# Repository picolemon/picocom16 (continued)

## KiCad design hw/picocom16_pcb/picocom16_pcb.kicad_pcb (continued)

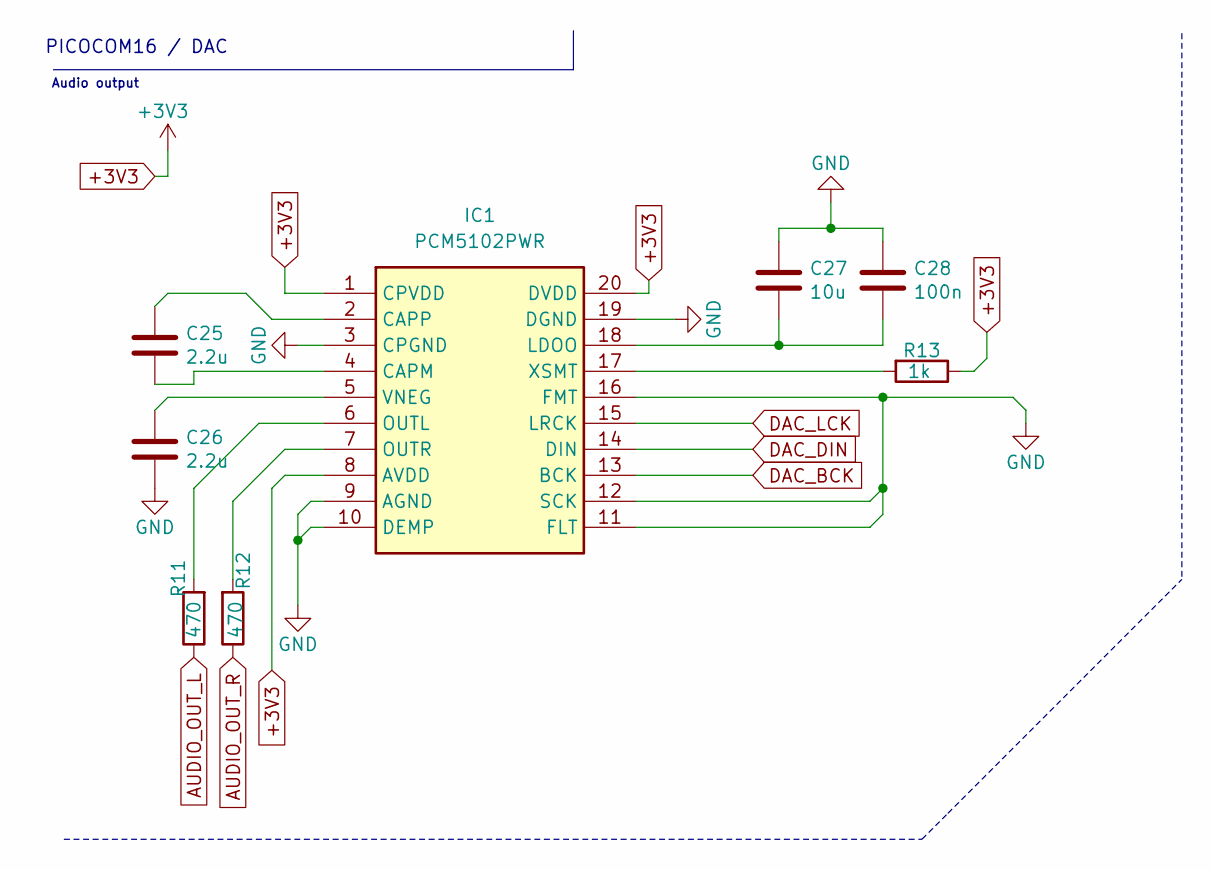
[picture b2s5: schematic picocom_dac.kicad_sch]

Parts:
C25, C26: 2.2u; C_0402_1005Metric
C27: 10u; C_0402_1005Metric
C28: 100n; C_0402_1005Metric
IC1: PCM5102PWR; SOP65P640X120-20N; Mouser Part Number 595-PCM5102PWR
R11, R12: 470; R_0402_1005Metric
R13: 1k; R_0402_1005Metric

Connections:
+3V3: IC1.1 (CPVDD), IC1.8 (AVDD), IC1.20 (DVDD), R13.1; also elsewhere on the board
AUDIO_OUT_L: R11.1; also elsewhere on the board
AUDIO_OUT_R: R12.1; also elsewhere on the board
DAC_BCK: IC1.13 (BCK); also elsewhere on the board
DAC_DIN: IC1.14 (DIN); also elsewhere on the board
DAC_LCK: IC1.15 (LRCK); also elsewhere on the board
GND: C26.2, C27.1, C28.1, IC1.3 (CPGND), IC1.9 (AGND), IC1.10 (DEMP), IC1.11 (FLT), IC1.12 (SCK), IC1.16 (FMT), IC1.19 (DGND); also elsewhere on the board
unnamed: C25.2, IC1.4 (CAPM)
unnamed: C25.1, IC1.2 (CAPP)
unnamed: C27.2, C28.2, IC1.18 (LDOO)
unnamed: IC1.6 (OUTL), R11.2
unnamed: IC1.7 (OUTR), R12.2
unnamed: C26.1, IC1.5 (VNEG)
unnamed: IC1.17 (XSMT), R13.2

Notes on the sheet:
PICOCOM16 / DAC
Audio output

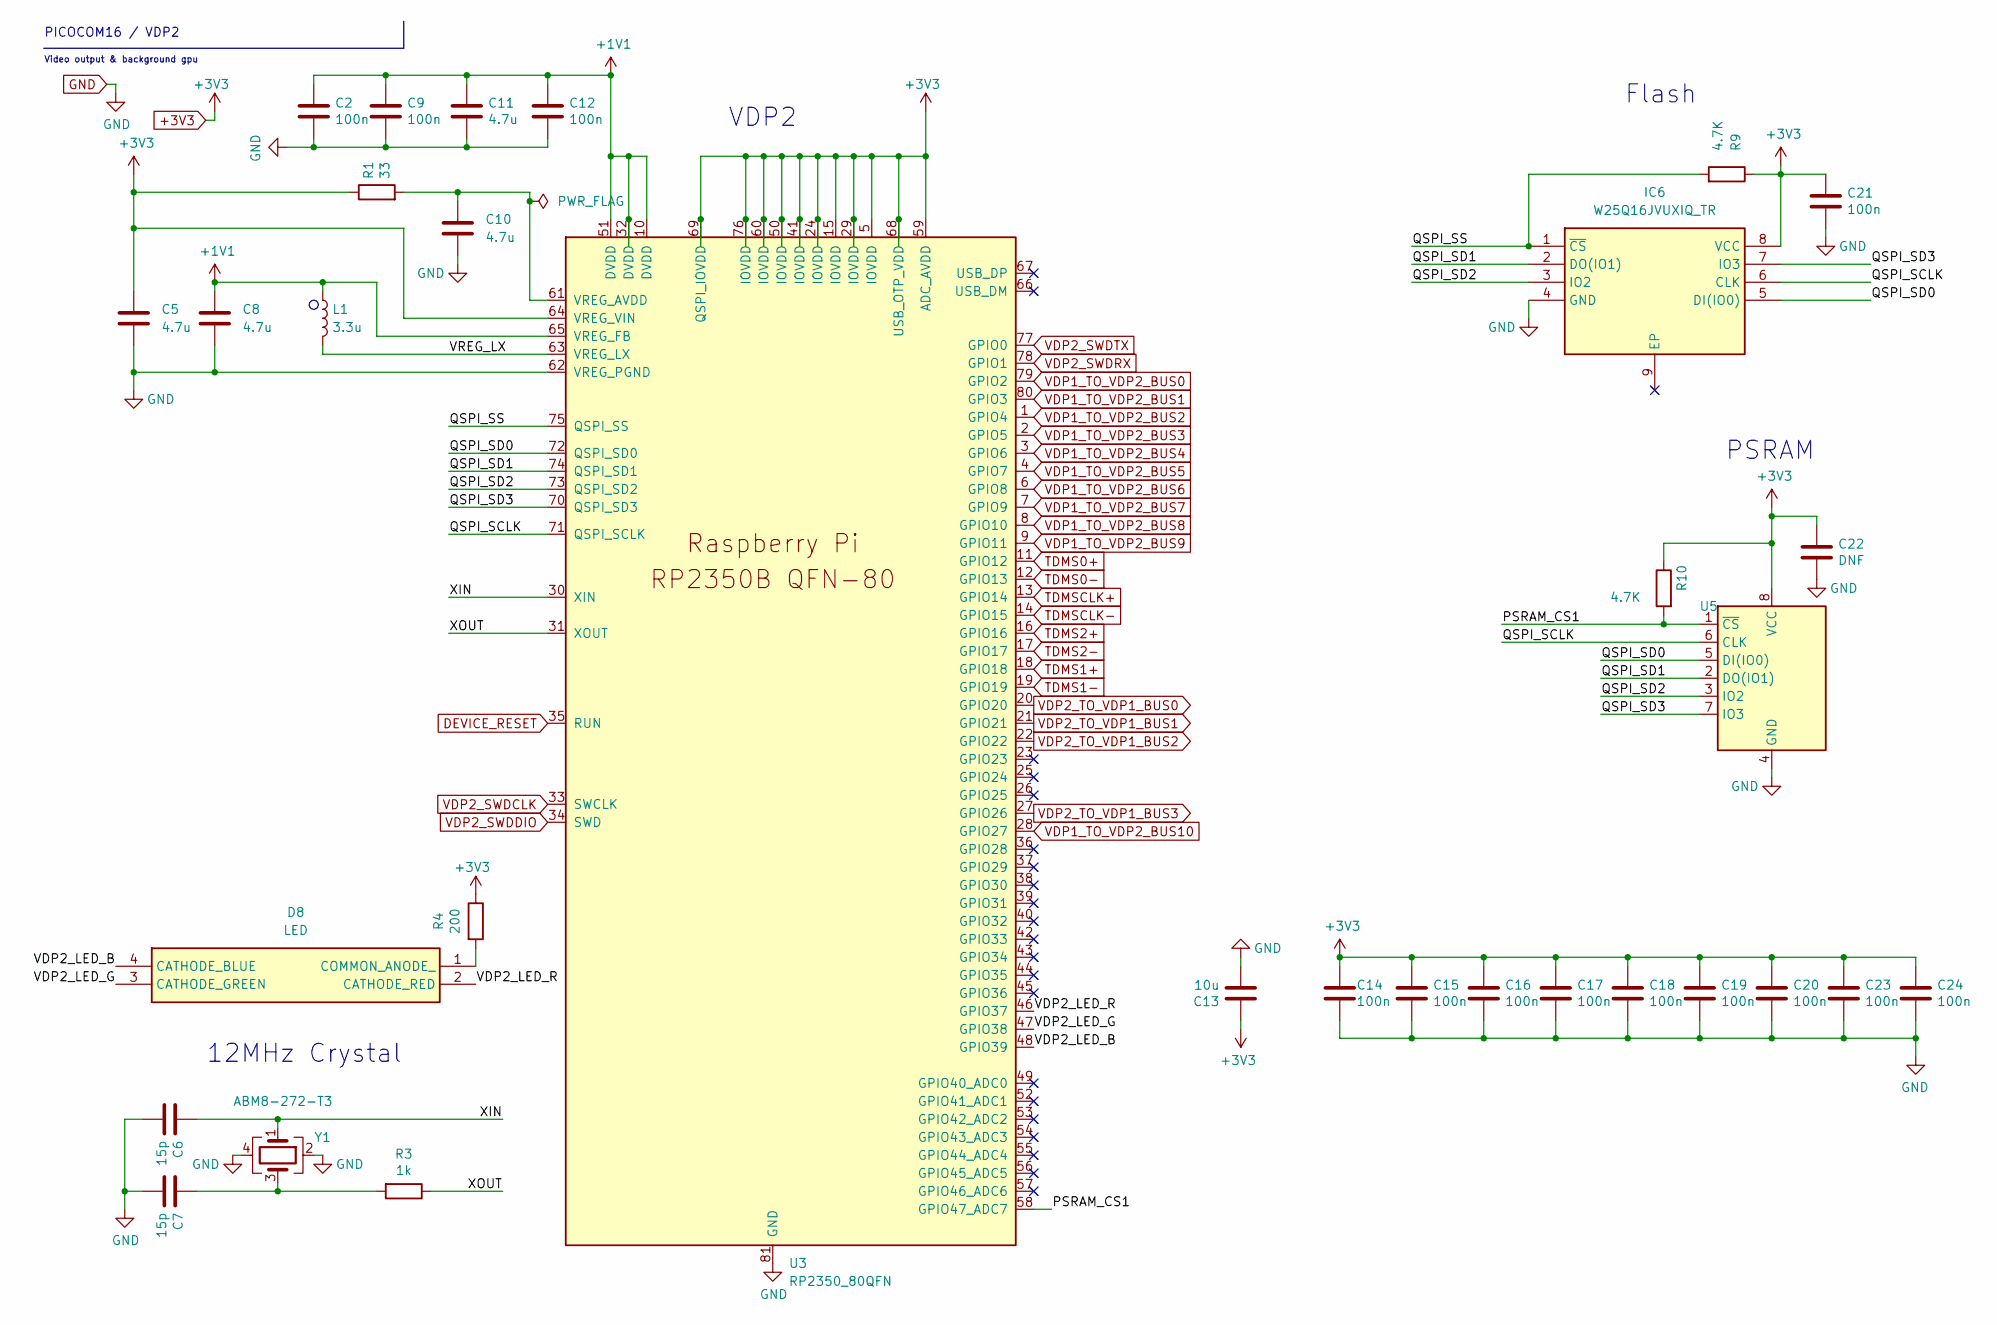
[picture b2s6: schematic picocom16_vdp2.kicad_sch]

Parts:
C2, C9, C12, C14, C15, C16, C17, C18, C19, C20, C21, C23, C24: 100n; C_0402_1005Metric
C5, C8, C10, C11: 4.7u; C_0402_1005Metric
C6, C7: 15p; C_0402_1005Metric
C13: 10u; C_0805_2012Metric
C22: DNF; C_0402_1005Metric
D8: LRTBR48G-P9Q7-1+R7S5-26+NP-68; LRTBR48GP9Q71R7S526NP68; Mouser Part Number 720-LRTBR48GP9A3521
IC6: W25Q16JVUXIQ_TR; SON50P300X200X60-9N; Mouser Part Number 454-W25Q16JVUXIQTR
L1: 3.3u; L_0805_2012Metric
R1: 33; R_0402_1005Metric
R3: 1k; R_0402_1005Metric
R4: 200; R_0402_1005Metric
R9, R10: 4.7K; R_0402_1005Metric
U3: RP2350_80QFN; RP2350-QFN-80-1EP_10x10_P0.4mm_EP3.4x3.4mm_ThermalVias
U5: SOIC-8_5.23x5.23mm_P1.27mm
Y1: ABM8-272-T3; ABM8272T3

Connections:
+1V1: C2.1, C8.1, C9.1, C11.1, C12.1, L1.1, U3.10 (DVDD), U3.32 (DVDD), U3.51 (DVDD), U3.65 (VREG_FB); also elsewhere on the board
+3V3: C5.1, C13.1, C14.1, C15.1, C16.1, C17.1, C18.1, C19.1, C20.1, C21.1, C22.1, C23.1, C24.1, IC6.8 (VCC), R1.1, R4.1, R9.1, R10.1, U3.5 (IOVDD), U3.15 (IOVDD), U3.24 (IOVDD), U3.29 (IOVDD), U3.41 (IOVDD), U3.50 (IOVDD), U3.59 (ADC_AVDD), U3.60 (IOVDD), U3.64 (VREG_VIN), U3.68 (USB_OTP_VDD), U3.69 (QSPI_IOVDD), U3.76 (IOVDD), U5.8 (VCC); also elsewhere on the board
/VDP2/PSRAM_CS1: R10.2, U3.58 (GPIO47_ADC7), U5.1 (~CS)
/VDP2/QSPI_SCLK: IC6.6 (CLK), U3.71 (QSPI_SCLK), U5.6 (CLK)
/VDP2/QSPI_SD0: IC6.5 (DI(IO0)), U3.72 (QSPI_SD0), U5.5 (DI(IO0))
/VDP2/QSPI_SD1: IC6.2 (DO(IO1)), U3.74 (QSPI_SD1), U5.2 (DO(IO1))
/VDP2/QSPI_SD2: IC6.3 (IO2), U3.73 (QSPI_SD2), U5.3 (IO2)
/VDP2/QSPI_SD3: IC6.7 (IO3), U3.70 (QSPI_SD3), U5.7 (IO3)
/VDP2/QSPI_SS: IC6.1 (~CS), R9.2, U3.75 (QSPI_SS)
/VDP2/VDP2_LED_B: D8.4 (CATHODE_BLUE), U3.48 (GPIO39)
/VDP2/VDP2_LED_G: D8.3 (CATHODE_GREEN), U3.47 (GPIO38)
/VDP2/VDP2_LED_R: D8.2 (CATHODE_RED), U3.46 (GPIO37)
/VDP2/VREG_LX: L1.2, U3.63 (VREG_LX)
/VDP2/XIN: C6.1, U3.30 (XIN), Y1.1
/VDP2/XOUT: R3.1, U3.31 (XOUT)
DEVICE_RESET: U3.35 (RUN); also elsewhere on the board
GND: C2.2, C5.2, C6.2, C7.2, C8.2, C9.2, C10.2, C11.2, C12.2, C13.2, C14.2, C15.2, C16.2, C17.2, C18.2, C19.2, C20.2, C21.2, C22.2, C23.2, C24.2, IC6.4 (GND), U3.62 (VREG_PGND), U3.81 (GND), U5.4 (GND), Y1.2, Y1.4; also elsewhere on the board
unnamed: C7.1, R3.2, Y1.3
unnamed: D8.1 (COMMON_ANODE_), R4.2
unnamed: C10.1, R1.2, U3.61 (VREG_AVDD)
TDMS0+: U3.11 (GPIO12); also elsewhere on the board
TDMS0-: U3.12 (GPIO13); also elsewhere on the board
TDMS1+: U3.18 (GPIO18); also elsewhere on the board
TDMS1-: U3.19 (GPIO19); also elsewhere on the board
TDMS2+: U3.16 (GPIO16); also elsewhere on the board
TDMS2-: U3.17 (GPIO17); also elsewhere on the board
TDMSCLK+: U3.13 (GPIO14); also elsewhere on the board
TDMSCLK-: U3.14 (GPIO15); also elsewhere on the board
VDP1_TO_VDP2_BUS0: U3.79 (GPIO2); also elsewhere on the board
VDP1_TO_VDP2_BUS1: U3.80 (GPIO3); also elsewhere on the board
VDP1_TO_VDP2_BUS2: U3.1 (GPIO4); also elsewhere on the board
VDP1_TO_VDP2_BUS3: U3.2 (GPIO5); also elsewhere on the board
VDP1_TO_VDP2_BUS4: U3.3 (GPIO6); also elsewhere on the board
VDP1_TO_VDP2_BUS5: U3.4 (GPIO7); also elsewhere on the board
VDP1_TO_VDP2_BUS6: U3.6 (GPIO8); also elsewhere on the board
VDP1_TO_VDP2_BUS7: U3.7 (GPIO9); also elsewhere on the board
VDP1_TO_VDP2_BUS8: U3.8 (GPIO10); also elsewhere on the board
VDP1_TO_VDP2_BUS9: U3.9 (GPIO11); also elsewhere on the board
VDP1_TO_VDP2_BUS10: U3.28 (GPIO27); also elsewhere on the board
VDP2_SWDCLK: U3.33 (SWCLK); also elsewhere on the board
VDP2_SWDDIO: U3.34 (SWD); also elsewhere on the board
VDP2_SWDRX: U3.78 (GPIO1); also elsewhere on the board
VDP2_SWDTX: U3.77 (GPIO0); also elsewhere on the board
VDP2_TO_VDP1_BUS0: U3.20 (GPIO20); also elsewhere on the board
VDP2_TO_VDP1_BUS1: U3.21 (GPIO21); also elsewhere on the board
VDP2_TO_VDP1_BUS2: U3.22 (GPIO22); also elsewhere on the board
VDP2_TO_VDP1_BUS3: U3.27 (GPIO26); also elsewhere on the board

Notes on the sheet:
PSRAM
Flash
VDP2
12MHz Crystal
PICOCOM16 / VDP2
Video output & background gpu

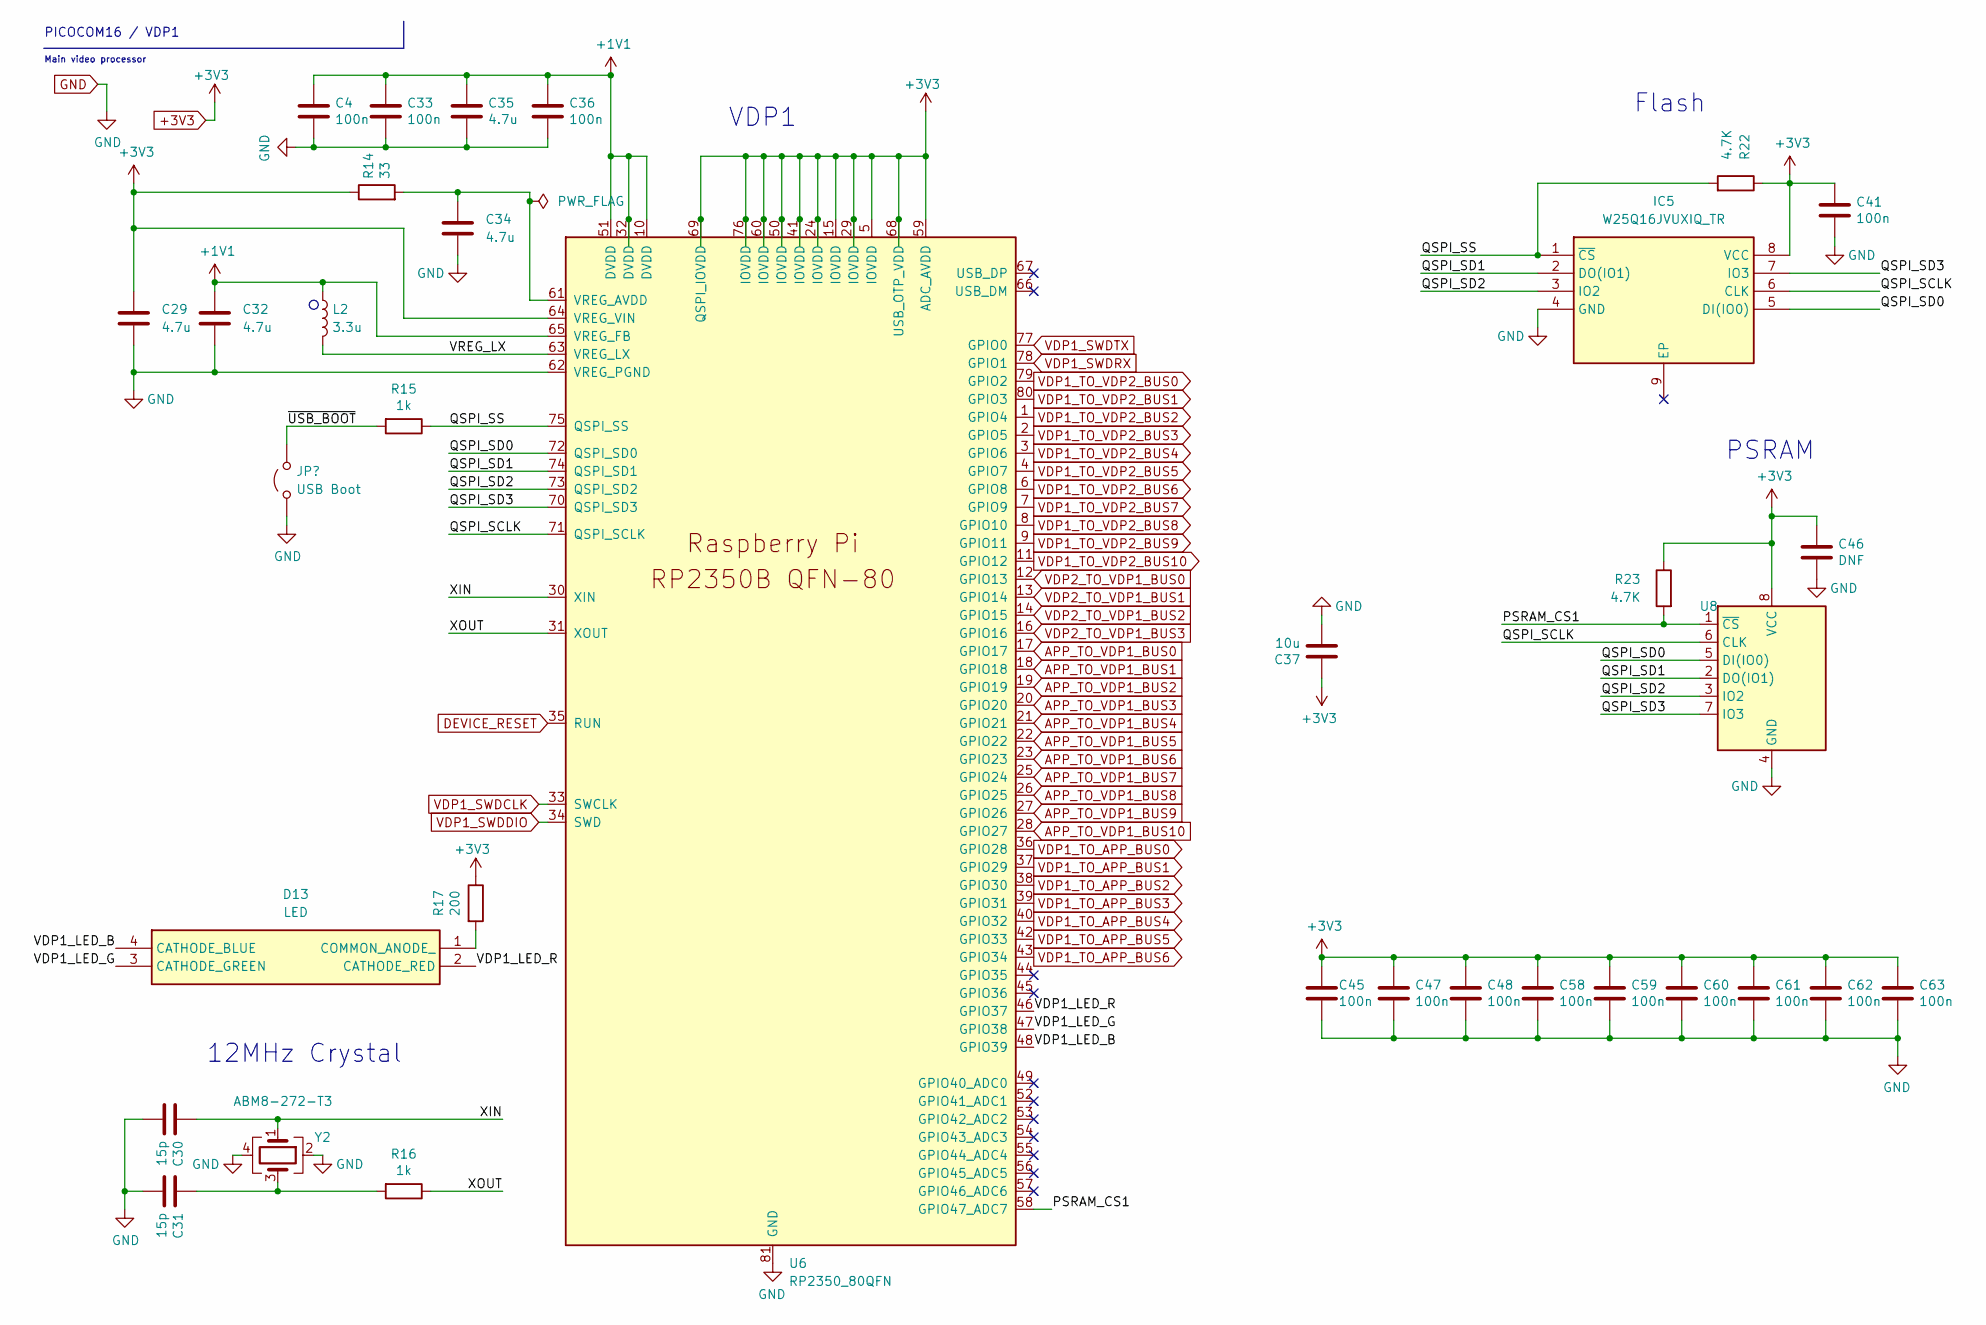
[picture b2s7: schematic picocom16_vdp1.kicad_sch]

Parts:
C4, C33, C36, C41, C45, C47, C48, C58, C59, C60, C61, C62, C63: 100n; C_0402_1005Metric
C29, C32, C34, C35: 4.7u; C_0402_1005Metric
C30, C31: 15p; C_0402_1005Metric
C37: 10u; C_0805_2012Metric
C46: DNF; C_0402_1005Metric
D13: LRTBR48G-P9Q7-1+R7S5-26+NP-68; LRTBR48GP9Q71R7S526NP68; Mouser Part Number 720-LRTBR48GP9A3521
IC5: W25Q16JVUXIQ_TR; SON50P300X200X60-9N; Mouser Part Number 454-W25Q16JVUXIQTR
JP2: USB Boot; SolderJumper-2_P1.3mm_Open_Pad1.0x1.5mm
L2: 3.3u; L_0805_2012Metric
R14: 33; R_0402_1005Metric
R15, R16: 1k; R_0402_1005Metric
R17: 200; R_0402_1005Metric
R22, R23: 4.7K; R_0402_1005Metric
U6: RP2350_80QFN; RP2350-QFN-80-1EP_10x10_P0.4mm_EP3.4x3.4mm_ThermalVias
U8: SOIC-8_5.23x5.23mm_P1.27mm
Y2: ABM8-272-T3; ABM8272T3

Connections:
+1V1: C4.1, C32.1, C33.1, C35.1, C36.1, L2.1, U6.10 (DVDD), U6.32 (DVDD), U6.51 (DVDD), U6.65 (VREG_FB); also elsewhere on the board
+3V3: C29.1, C37.1, C41.1, C45.1, C46.1, C47.1, C48.1, C58.1, C59.1, C60.1, C61.1, C62.1, C63.1, IC5.8 (VCC), R14.1, R17.1, R22.1, R23.1, U6.5 (IOVDD), U6.15 (IOVDD), U6.24 (IOVDD), U6.29 (IOVDD), U6.41 (IOVDD), U6.50 (IOVDD), U6.59 (ADC_AVDD), U6.60 (IOVDD), U6.64 (VREG_VIN), U6.68 (USB_OTP_VDD), U6.69 (QSPI_IOVDD), U6.76 (IOVDD), U8.8 (VCC); also elsewhere on the board
/VDP1/PSRAM_CS1: R23.2, U6.58 (GPIO47_ADC7), U8.1 (~CS)
/VDP1/QSPI_SCLK: IC5.6 (CLK), U6.71 (QSPI_SCLK), U8.6 (CLK)
/VDP1/QSPI_SD0: IC5.5 (DI(IO0)), U6.72 (QSPI_SD0), U8.5 (DI(IO0))
/VDP1/QSPI_SD1: IC5.2 (DO(IO1)), U6.74 (QSPI_SD1), U8.2 (DO(IO1))
/VDP1/QSPI_SD2: IC5.3 (IO2), U6.73 (QSPI_SD2), U8.3 (IO2)
/VDP1/QSPI_SD3: IC5.7 (IO3), U6.70 (QSPI_SD3), U8.7 (IO3)
/VDP1/QSPI_SS: IC5.1 (~CS), R15.1, R22.2, U6.75 (QSPI_SS)
/VDP1/VDP1_LED_B: D13.4 (CATHODE_BLUE), U6.48 (GPIO39)
/VDP1/VDP1_LED_G: D13.3 (CATHODE_GREEN), U6.47 (GPIO38)
/VDP1/VDP1_LED_R: D13.2 (CATHODE_RED), U6.46 (GPIO37)
/VDP1/VREG_LX: L2.2, U6.63 (VREG_LX)
/VDP1/XIN: C30.1, U6.30 (XIN), Y2.1
/VDP1/XOUT: R16.1, U6.31 (XOUT)
/VDP1/~USB_BOOT: JP2.2 (B), R15.2
APP_TO_VDP1_BUS0: U6.17 (GPIO17); also elsewhere on the board
APP_TO_VDP1_BUS1: U6.18 (GPIO18); also elsewhere on the board
APP_TO_VDP1_BUS2: U6.19 (GPIO19); also elsewhere on the board
APP_TO_VDP1_BUS3: U6.20 (GPIO20); also elsewhere on the board
APP_TO_VDP1_BUS4: U6.21 (GPIO21); also elsewhere on the board
APP_TO_VDP1_BUS5: U6.22 (GPIO22); also elsewhere on the board
APP_TO_VDP1_BUS6: U6.23 (GPIO23); also elsewhere on the board
APP_TO_VDP1_BUS7: U6.25 (GPIO24); also elsewhere on the board
APP_TO_VDP1_BUS8: U6.26 (GPIO25); also elsewhere on the board
APP_TO_VDP1_BUS9: U6.27 (GPIO26); also elsewhere on the board
APP_TO_VDP1_BUS10: U6.28 (GPIO27); also elsewhere on the board
DEVICE_RESET: U6.35 (RUN); also elsewhere on the board
GND: C4.2, C29.2, C30.2, C31.2, C32.2, C33.2, C34.2, C35.2, C36.2, C37.2, C41.2, C45.2, C46.2, C47.2, C48.2, C58.2, C59.2, C60.2, C61.2, C62.2, C63.2, IC5.4 (GND), JP2.1 (A), U6.62 (VREG_PGND), U6.81 (GND), U8.4 (GND), Y2.2, Y2.4; also elsewhere on the board
unnamed: C31.1, R16.2, Y2.3
unnamed: D13.1 (COMMON_ANODE_), R17.2
unnamed: C34.1, R14.2, U6.61 (VREG_AVDD)
VDP1_SWDCLK: U6.33 (SWCLK); also elsewhere on the board
VDP1_SWDDIO: U6.34 (SWD); also elsewhere on the board
VDP1_SWDRX: U6.78 (GPIO1); also elsewhere on the board
VDP1_SWDTX: U6.77 (GPIO0); also elsewhere on the board
VDP1_TO_APP_BUS0: U6.36 (GPIO28); also elsewhere on the board
VDP1_TO_APP_BUS1: U6.37 (GPIO29); also elsewhere on the board
VDP1_TO_APP_BUS2: U6.38 (GPIO30); also elsewhere on the board
VDP1_TO_APP_BUS3: U6.39 (GPIO31); also elsewhere on the board
VDP1_TO_APP_BUS4: U6.40 (GPIO32); also elsewhere on the board
VDP1_TO_APP_BUS5: U6.42 (GPIO33); also elsewhere on the board
VDP1_TO_APP_BUS6: U6.43 (GPIO34); also elsewhere on the board
VDP1_TO_VDP2_BUS0: U6.79 (GPIO2); also elsewhere on the board
VDP1_TO_VDP2_BUS1: U6.80 (GPIO3); also elsewhere on the board
VDP1_TO_VDP2_BUS2: U6.1 (GPIO4); also elsewhere on the board
VDP1_TO_VDP2_BUS3: U6.2 (GPIO5); also elsewhere on the board
VDP1_TO_VDP2_BUS4: U6.3 (GPIO6); also elsewhere on the board
VDP1_TO_VDP2_BUS5: U6.4 (GPIO7); also elsewhere on the board
VDP1_TO_VDP2_BUS6: U6.6 (GPIO8); also elsewhere on the board
VDP1_TO_VDP2_BUS7: U6.7 (GPIO9); also elsewhere on the board
VDP1_TO_VDP2_BUS8: U6.8 (GPIO10); also elsewhere on the board
VDP1_TO_VDP2_BUS9: U6.9 (GPIO11); also elsewhere on the board
VDP1_TO_VDP2_BUS10: U6.11 (GPIO12); also elsewhere on the board
VDP2_TO_VDP1_BUS0: U6.12 (GPIO13); also elsewhere on the board
VDP2_TO_VDP1_BUS1: U6.13 (GPIO14); also elsewhere on the board
VDP2_TO_VDP1_BUS2: U6.14 (GPIO15); also elsewhere on the board
VDP2_TO_VDP1_BUS3: U6.16 (GPIO16); also elsewhere on the board

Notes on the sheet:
PSRAM
Flash
VDP1
12MHz Crystal
PICOCOM16 / VDP1
Main video processor

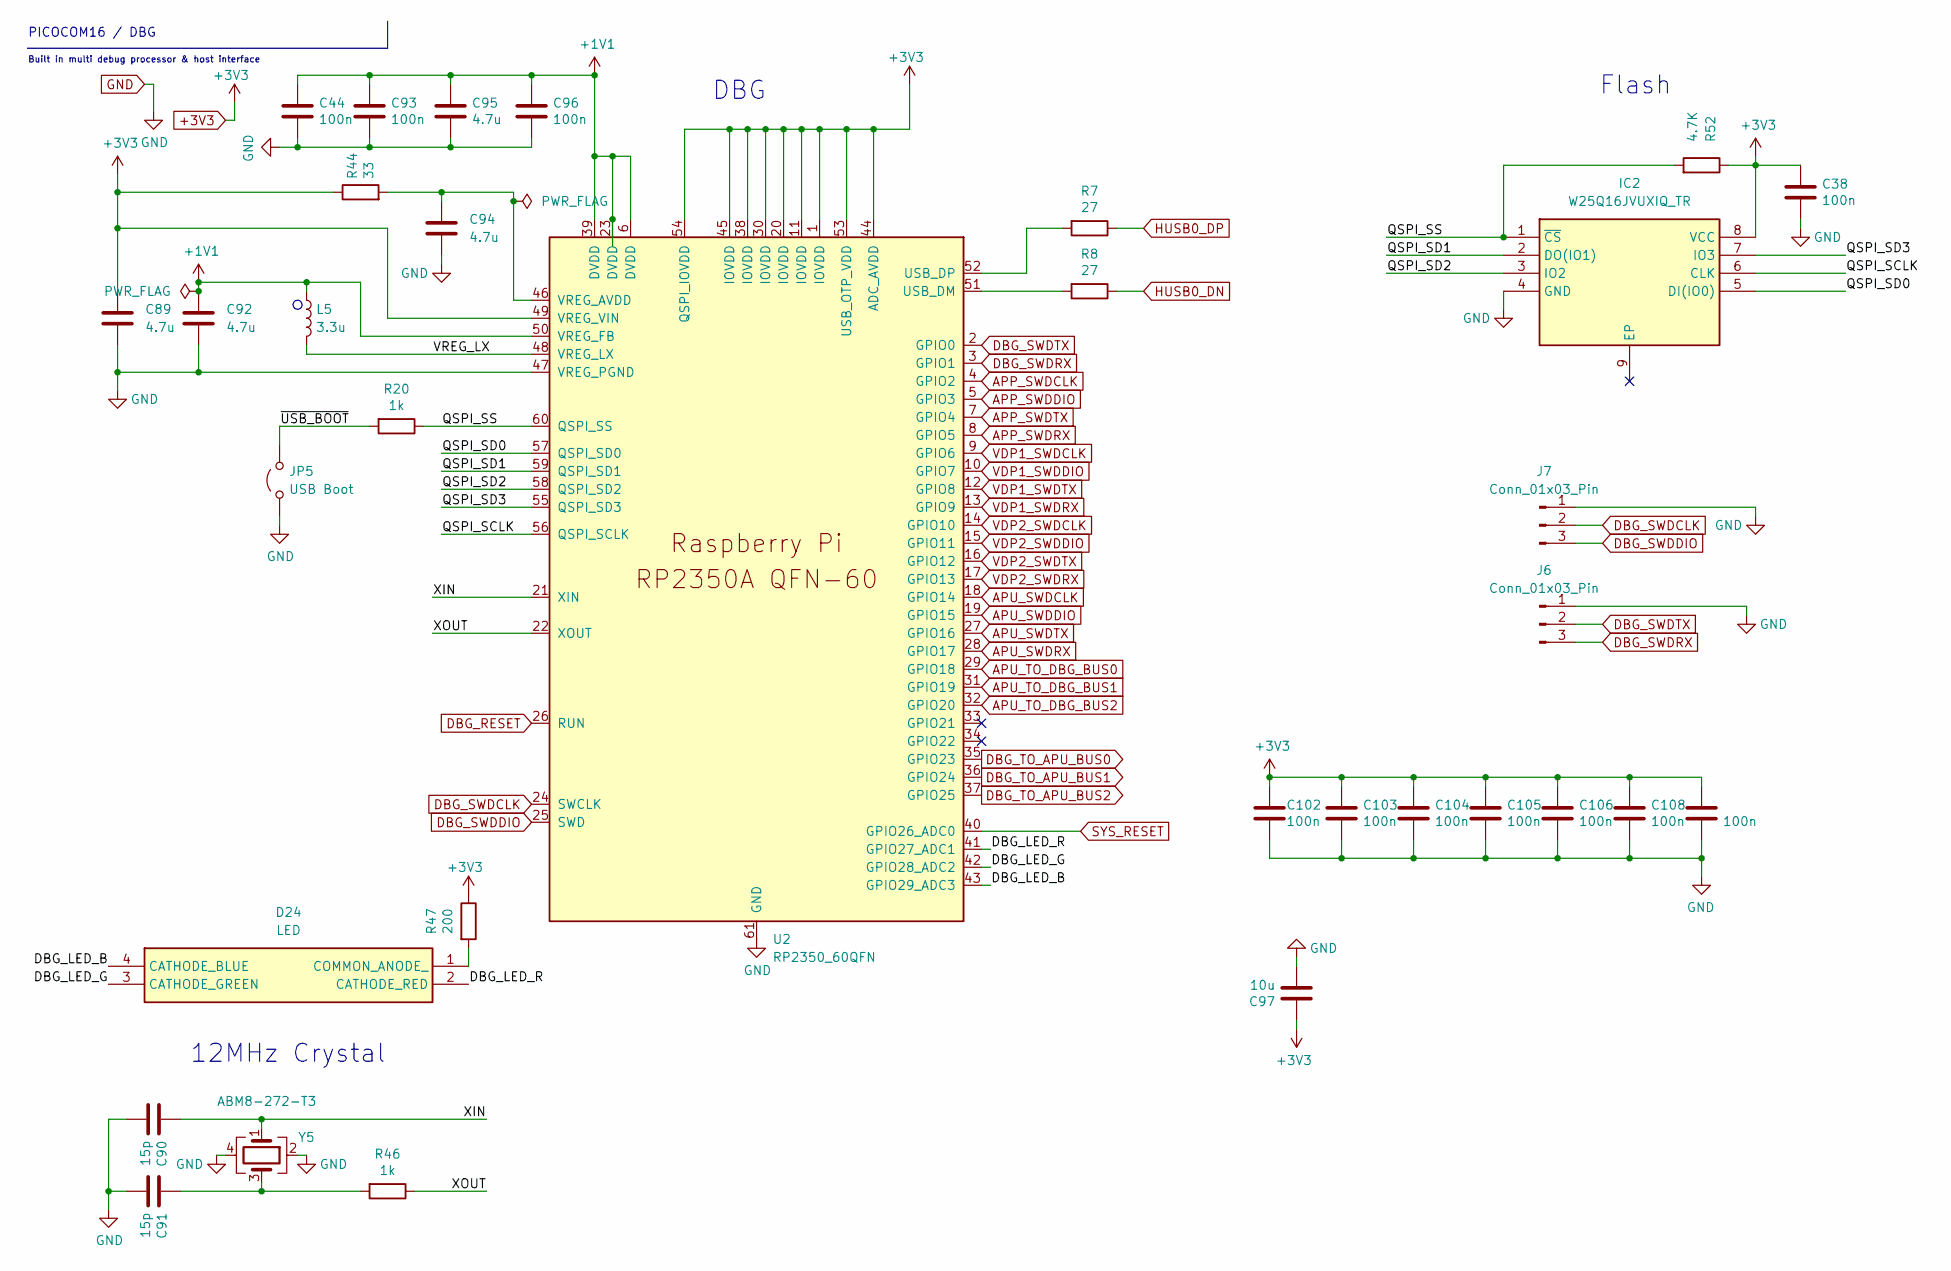
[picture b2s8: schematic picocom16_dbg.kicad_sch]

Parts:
C38, C44, C93, C96, C102, C103, C104, C105, C106, C108, C109: 100n; C_0402_1005Metric
C89, C92, C94, C95: 4.7u; C_0402_1005Metric
C90, C91: 15p; C_0402_1005Metric
C97: 10u; C_0805_2012Metric
D24: LRTBR48G-P9Q7-1+R7S5-26+NP-68; LRTBR48GP9Q71R7S526NP68; Mouser Part Number 720-LRTBR48GP9A3521
IC2: W25Q16JVUXIQ_TR; SON50P300X200X60-9N; Mouser Part Number 454-W25Q16JVUXIQTR
J6, J7: Conn_01x03_Pin; PinHeader_1x03_P2.54mm_Vertical_SMD_Pin1Left
JP5: USB Boot; SolderJumper-2_P1.3mm_Open_Pad1.0x1.5mm
L5: 3.3u; L_0805_2012Metric
R7, R8: 27; R_0402_1005Metric
R20, R46: 1k; R_0402_1005Metric
R44: 33; R_0402_1005Metric
R47: 200; R_0402_1005Metric
R52: 4.7K; R_0402_1005Metric
U2: RP2350_60QFN; QFN-60-1EP_7x7mm_P0.4mm_EP3.4x3.4mm
Y5: ABM8-272-T3; ABM8272T3

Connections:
+1V1: C44.1, C92.1, C93.1, C95.1, C96.1, L5.1, U2.6 (DVDD), U2.23 (DVDD), U2.39 (DVDD), U2.50 (VREG_FB); also elsewhere on the board
+3V3: C38.1, C89.1, C97.1, C102.1, C103.1, C104.1, C105.1, C106.1, C108.1, C109.1, IC2.8 (VCC), R44.1, R47.1, R52.1, U2.1 (IOVDD), U2.11 (IOVDD), U2.20 (IOVDD), U2.30 (IOVDD), U2.38 (IOVDD), U2.44 (ADC_AVDD), U2.45 (IOVDD), U2.49 (VREG_VIN), U2.53 (USB_OTP_VDD), U2.54 (QSPI_IOVDD); also elsewhere on the board
/DBG/DBG_LED_B: D24.4 (CATHODE_BLUE), U2.43 (GPIO29_ADC3)
/DBG/DBG_LED_G: D24.3 (CATHODE_GREEN), U2.42 (GPIO28_ADC2)
/DBG/DBG_LED_R: D24.2 (CATHODE_RED), U2.41 (GPIO27_ADC1)
/DBG/QSPI_SCLK: IC2.6 (CLK), U2.56 (QSPI_SCLK)
/DBG/QSPI_SD0: IC2.5 (DI(IO0)), U2.57 (QSPI_SD0)
/DBG/QSPI_SD1: IC2.2 (DO(IO1)), U2.59 (QSPI_SD1)
/DBG/QSPI_SD2: IC2.3 (IO2), U2.58 (QSPI_SD2)
/DBG/QSPI_SD3: IC2.7 (IO3), U2.55 (QSPI_SD3)
/DBG/QSPI_SS: IC2.1 (~CS), R20.1, R52.2, U2.60 (QSPI_SS)
/DBG/VREG_LX: L5.2, U2.48 (VREG_LX)
/DBG/XIN: C90.1, U2.21 (XIN), Y5.1
/DBG/XOUT: R46.1, U2.22 (XOUT)
/DBG/~USB_BOOT: JP5.2 (B), R20.2
APP_SWDCLK: U2.4 (GPIO2); also elsewhere on the board
APP_SWDDIO: U2.5 (GPIO3); also elsewhere on the board
APP_SWDRX: U2.8 (GPIO5); also elsewhere on the board
APP_SWDTX: U2.7 (GPIO4); also elsewhere on the board
APU_SWDCLK: U2.18 (GPIO14); also elsewhere on the board
APU_SWDDIO: U2.19 (GPIO15); also elsewhere on the board
APU_SWDRX: U2.28 (GPIO17); also elsewhere on the board
APU_SWDTX: U2.27 (GPIO16); also elsewhere on the board
APU_TO_DBG_BUS0: U2.29 (GPIO18); also elsewhere on the board
APU_TO_DBG_BUS1: U2.31 (GPIO19); also elsewhere on the board
APU_TO_DBG_BUS2: U2.32 (GPIO20); also elsewhere on the board
DBG_RESET: U2.26 (RUN)
DBG_SWDCLK: J7.2, U2.24 (SWCLK)
DBG_SWDDIO: J7.3, U2.25 (SWD)
DBG_SWDRX: J6.3, U2.3 (GPIO1)
DBG_SWDTX: J6.2, U2.2 (GPIO0)
DBG_TO_APU_BUS0: U2.35 (GPIO23); also elsewhere on the board
DBG_TO_APU_BUS1: U2.36 (GPIO24); also elsewhere on the board
DBG_TO_APU_BUS2: U2.37 (GPIO25); also elsewhere on the board
GND: C38.2, C44.2, C89.2, C90.2, C91.2, C92.2, C93.2, C94.2, C95.2, C96.2, C97.2, C102.2, C103.2, C104.2, C105.2, C106.2, C108.2, C109.2, IC2.4 (GND), J6.1, J7.1, JP5.1 (A), U2.47 (VREG_PGND), U2.61 (GND), Y5.2, Y5.4; also elsewhere on the board
HUSB0_DN: R8.1; also elsewhere on the board
HUSB0_DP: R7.1; also elsewhere on the board
unnamed: C91.1, R46.2, Y5.3
unnamed: D24.1 (COMMON_ANODE_), R47.2
unnamed: R8.2, U2.51 (USB_DM)
unnamed: R7.2, U2.52 (USB_DP)
unnamed: C94.1, R44.2, U2.46 (VREG_AVDD)
SYS_RESET: U2.40 (GPIO26_ADC0); also elsewhere on the board
VDP1_SWDCLK: U2.9 (GPIO6); also elsewhere on the board
VDP1_SWDDIO: U2.10 (GPIO7); also elsewhere on the board
VDP1_SWDRX: U2.13 (GPIO9); also elsewhere on the board
VDP1_SWDTX: U2.12 (GPIO8); also elsewhere on the board
VDP2_SWDCLK: U2.14 (GPIO10); also elsewhere on the board
VDP2_SWDDIO: U2.15 (GPIO11); also elsewhere on the board
VDP2_SWDRX: U2.17 (GPIO13); also elsewhere on the board
VDP2_SWDTX: U2.16 (GPIO12); also elsewhere on the board

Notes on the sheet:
DBG
Flash
12MHz Crystal
PICOCOM16 / DBG
Built in multi debug processor & host interface

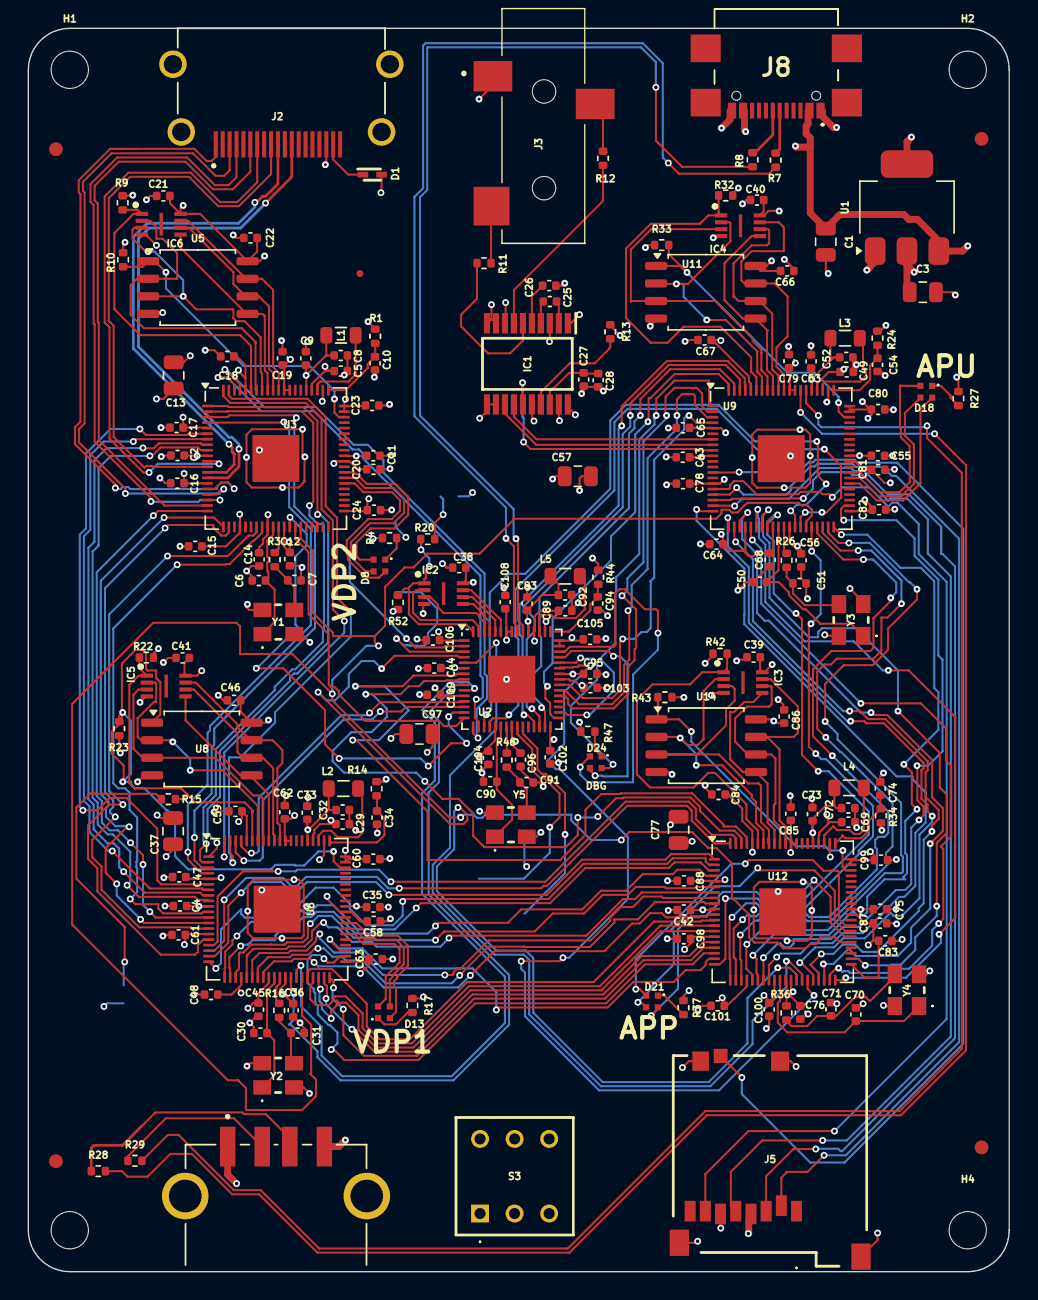
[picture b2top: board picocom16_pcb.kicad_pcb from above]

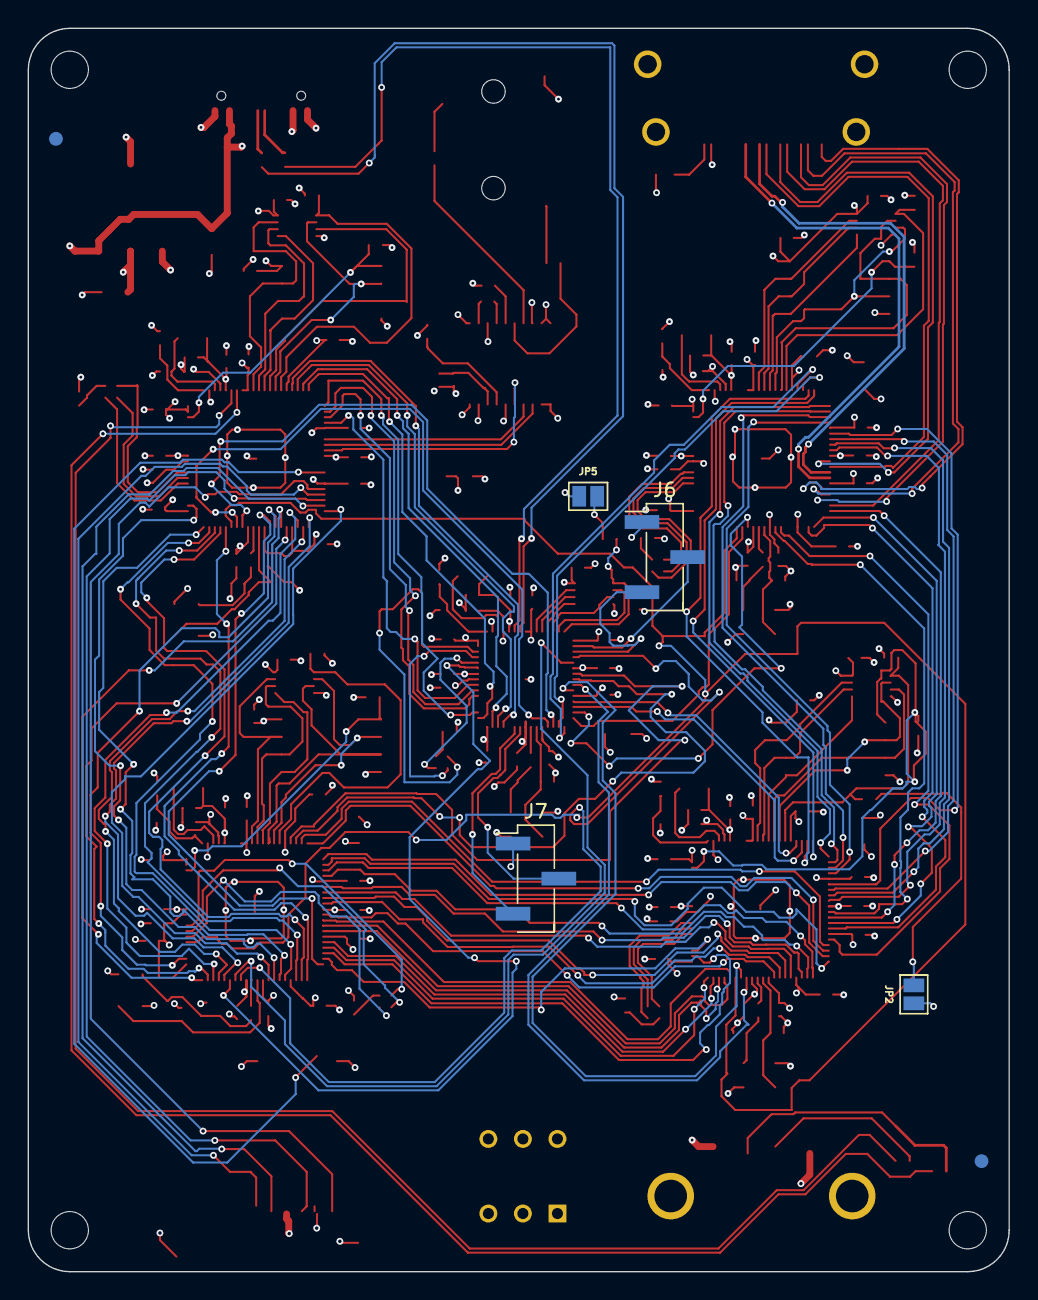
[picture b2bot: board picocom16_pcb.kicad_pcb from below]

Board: 4 copper layers, 71.0 x 90.0 mm, 194 parts (6 on the bottom side), 195 nets.

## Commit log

2026-02-07 init import with build guide
2026-02-07 added hw design kicad project files
2026-02-07 added sdk asset tools
2026-02-07 added thirdparty dependencies
2026-02-07 initial picocom sdk sources added
2026-02-07 gpu sources added
2026-02-07 plaform hw and simulation components
2026-02-07 cores components added and hw simulation support
2026-02-07 apu core project added
2026-02-07 added vdp1 and vdp2 core projects added
2026-02-07 libdvi license added
2026-02-07 demos added
2026-02-07 asset cleanup
2026-02-07 readme changes
2026-02-07 readme internal link fixes
2026-02-07 webgl sim compile fix and comment rant cleanup
2026-02-07 added minerload example game uf2 and fixed some internal links
2026-02-07 README text change
2026-02-17 added docs
2026-02-17 added firmware images
2026-02-17 added hw source
2026-02-17 added sdk
2026-02-17 added apu core
2026-02-17 added vdp1 core
2026-02-17 added vdp2 core
2026-02-17 added demos
